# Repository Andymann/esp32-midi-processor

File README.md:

# esp32-midi-processor

esp32-based multitool. Routing, merging, realtime-manipulation of MIDI-data.  
This repo contains code, kicad-files and a BOM for (nearly) one-click order at [pcbway](https://https://pcbway-com).  

Find more details on the project, instructions on how to order your own pcbs and more at https://andyland.info/wordpress/esp32-midi-processor/

If you directly want to order your set of PCBs for this project feel free to

<p style="text-align:center; </p>

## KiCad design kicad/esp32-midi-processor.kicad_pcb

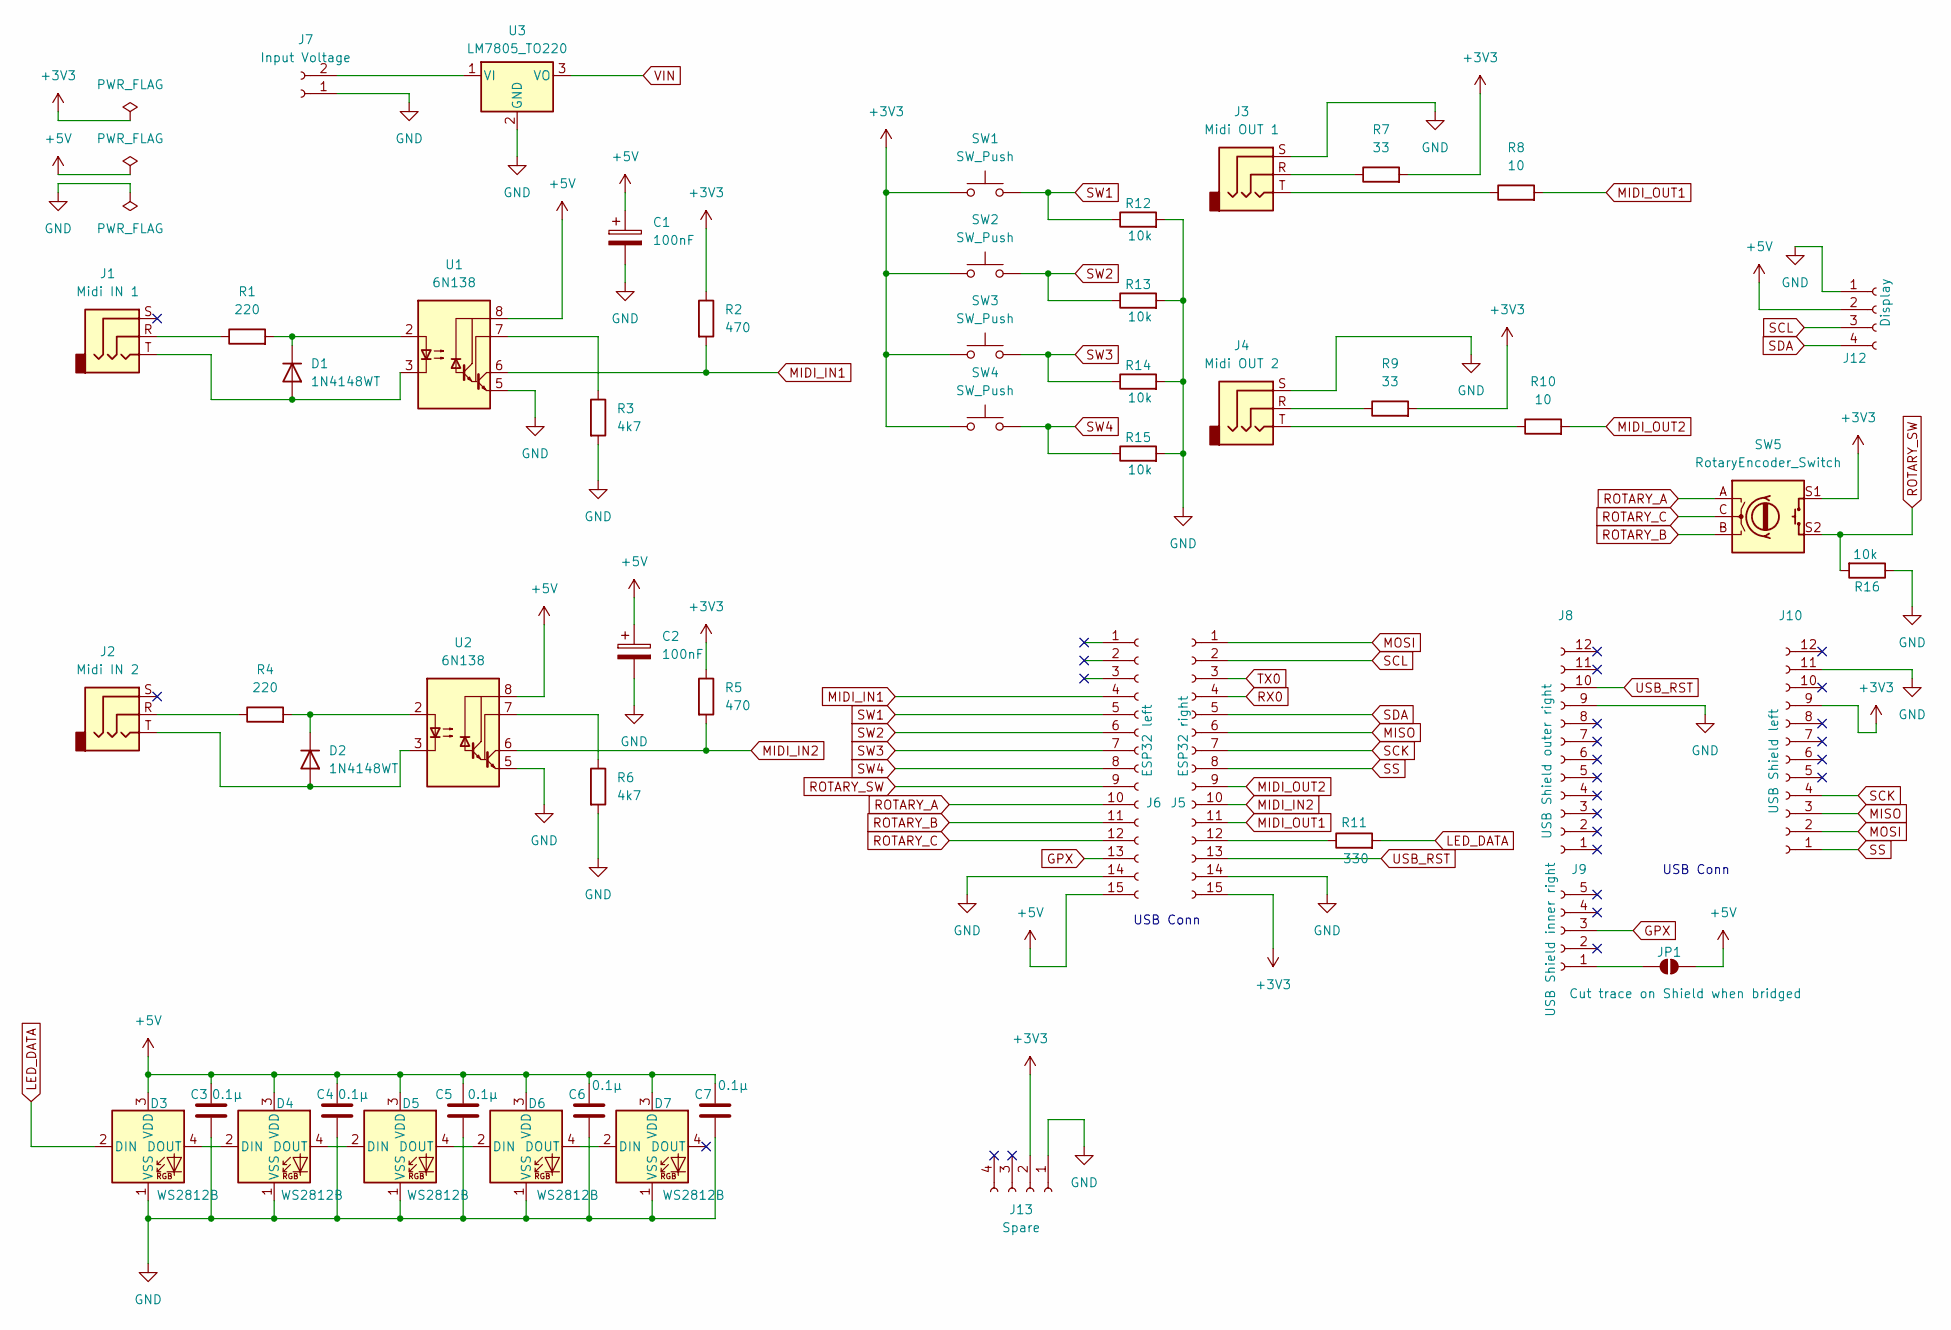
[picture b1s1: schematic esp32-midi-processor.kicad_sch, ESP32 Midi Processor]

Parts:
C1, C2: 100nF; C_0603_1608Metric
C3, C4, C5, C6, C7: 0.1µ; C_0603_1608Metric
D1, D2: 1N4148WT; D_SOD-523
D3, D4, D5, D6, D7: WS2812B; LED_WS2812B_PLCC4_5.0x5.0mm_P3.2mm
J1: Midi IN 1; Jack_3.5mm_CUI_SJ-3523-SMT_Horizontal
J2: Midi IN 2; Jack_3.5mm_CUI_SJ-3523-SMT_Horizontal
J3: Midi OUT 1; Jack_3.5mm_CUI_SJ-3523-SMT_Horizontal
J4: Midi OUT 2; Jack_3.5mm_CUI_SJ-3523-SMT_Horizontal
J5: ESP32 right; PinHeader_1x15_P2.54mm_Vertical
J6: ESP32 left; PinHeader_1x15_P2.54mm_Vertical
J7: Input Voltage; TerminalBlock_RND_205-00001_1x02_P5.00mm_Horizontal
J8: USB Shield outer right; PinHeader_1x12_P2.54mm_Vertical
J9: USB Shield inner right; PinHeader_1x05_P2.54mm_Vertical
J10: USB Shield left; PinHeader_1x12_P2.54mm_Vertical
J12: Display; PinHeader_1x04_P2.54mm_Vertical
J13: Spare; PinHeader_1x04_P2.54mm_Vertical
JP1: Cut trace on Shield when bridged; SolderJumper-2_P1.3mm_Open_RoundedPad1.0x1.5mm
R1, R4: 220; R_0603_1608Metric
R2, R5: 470; R_0603_1608Metric
R3, R6: 4k7; R_0603_1608Metric
R7, R9: 33; R_0603_1608Metric
R8, R10: 10; R_0603_1608Metric
R11: 330; R_0603_1608Metric
R12, R13, R14, R15, R16: 10k; R_0603_1608Metric
SW1, SW2, SW3, SW4: SW_Push; SW_PUSH-12mm_Wuerth-430476085716
SW5: RotaryEncoder_Switch; RotaryEncoder_Alps_EC11E-Switch_Vertical_H20mm
U1, U2: 6N138; SOP-8_6.605x9.655mm_P2.54mm
U3: LM7805_TO220; TO-220-3_Vertical

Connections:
+3V3: J5.15, J10.9, J13.2, R2.1, R5.1, R7.2, R9.2, SW1.1, SW2.1, SW3.1, SW4.1, SW5.S1
+5V: C1.1, C2.1, C3.1, C4.1, C5.1, C6.1, C7.1, D3.3 (VDD), D4.3 (VDD), D5.3 (VDD), D6.3 (VDD), D7.3 (VDD), J6.15, J12.2, JP1.2 (B), U1.8 (VCC), U2.8 (VCC)
GND: C1.2, C2.2, C3.2, C4.2, C5.2, C6.2, C7.2, D3.1 (VSS), D4.1 (VSS), D5.1 (VSS), D6.1 (VSS), D7.1 (VSS), J3.S, J4.S, J5.14, J6.14, J7.1, J8.9, J10.11, J12.1, J13.1, R3.2, R6.2, R12.2, R13.2, R14.2, R15.2, R16.1, U1.5 (GND), U2.5 (GND), U3.2 (GND)
GPX: J6.13, J9.3
LED_DATA: D3.2 (DIN), R11.2
MIDI_IN1: J6.4, R2.2, U1.6 (VO2)
MIDI_IN2: J5.10, R5.2, U2.6 (VO2)
MIDI_OUT1: J5.11, R8.2
MIDI_OUT2: J5.9, R10.2
MISO: J5.6, J10.3
MOSI: J5.1, J10.2
unnamed: D1.2 (A), J1.T, U1.3 (C2)
unnamed: D1.1 (K), R1.2, U1.2 (C1)
unnamed: D2.2 (A), J2.T, U2.3 (C2)
unnamed: D2.1 (K), R4.2, U2.2 (C1)
unnamed: D3.4 (DOUT), D4.2 (DIN)
unnamed: D4.4 (DOUT), D5.2 (DIN)
unnamed: D5.4 (DOUT), D6.2 (DIN)
unnamed: D6.4 (DOUT), D7.2 (DIN)
unnamed: J1.R, R1.1
unnamed: J2.R, R4.1
unnamed: J3.R, R7.1
unnamed: J3.T, R8.1
unnamed: J4.R, R9.1
unnamed: J4.T, R10.1
unnamed: J5.12, R11.1
unnamed: J7.2, U3.1 (VI)
unnamed: J9.1, JP1.1 (A)
unnamed: R3.1, U1.7 (VO1)
unnamed: R6.1, U2.7 (VO1)
ROTARY_A: J6.10, SW5.A
ROTARY_B: J6.11, SW5.B
ROTARY_C: J6.12, SW5.C
ROTARY_SW: J6.9, R16.2, SW5.S2
RX0: J5.4
SCK: J5.7, J10.4
SCL: J5.2, J12.3
SDA: J5.5, J12.4
SS: J5.8, J10.1
SW1: J6.5, R12.1, SW1.2
SW2: J6.6, R13.1, SW2.2
SW3: J6.7, R14.1, SW3.2
SW4: J6.8, R15.1, SW4.2
TX0: J5.3
USB_RST: J5.13, J8.10
VIN: U3.3 (VO)

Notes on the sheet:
USB Conn

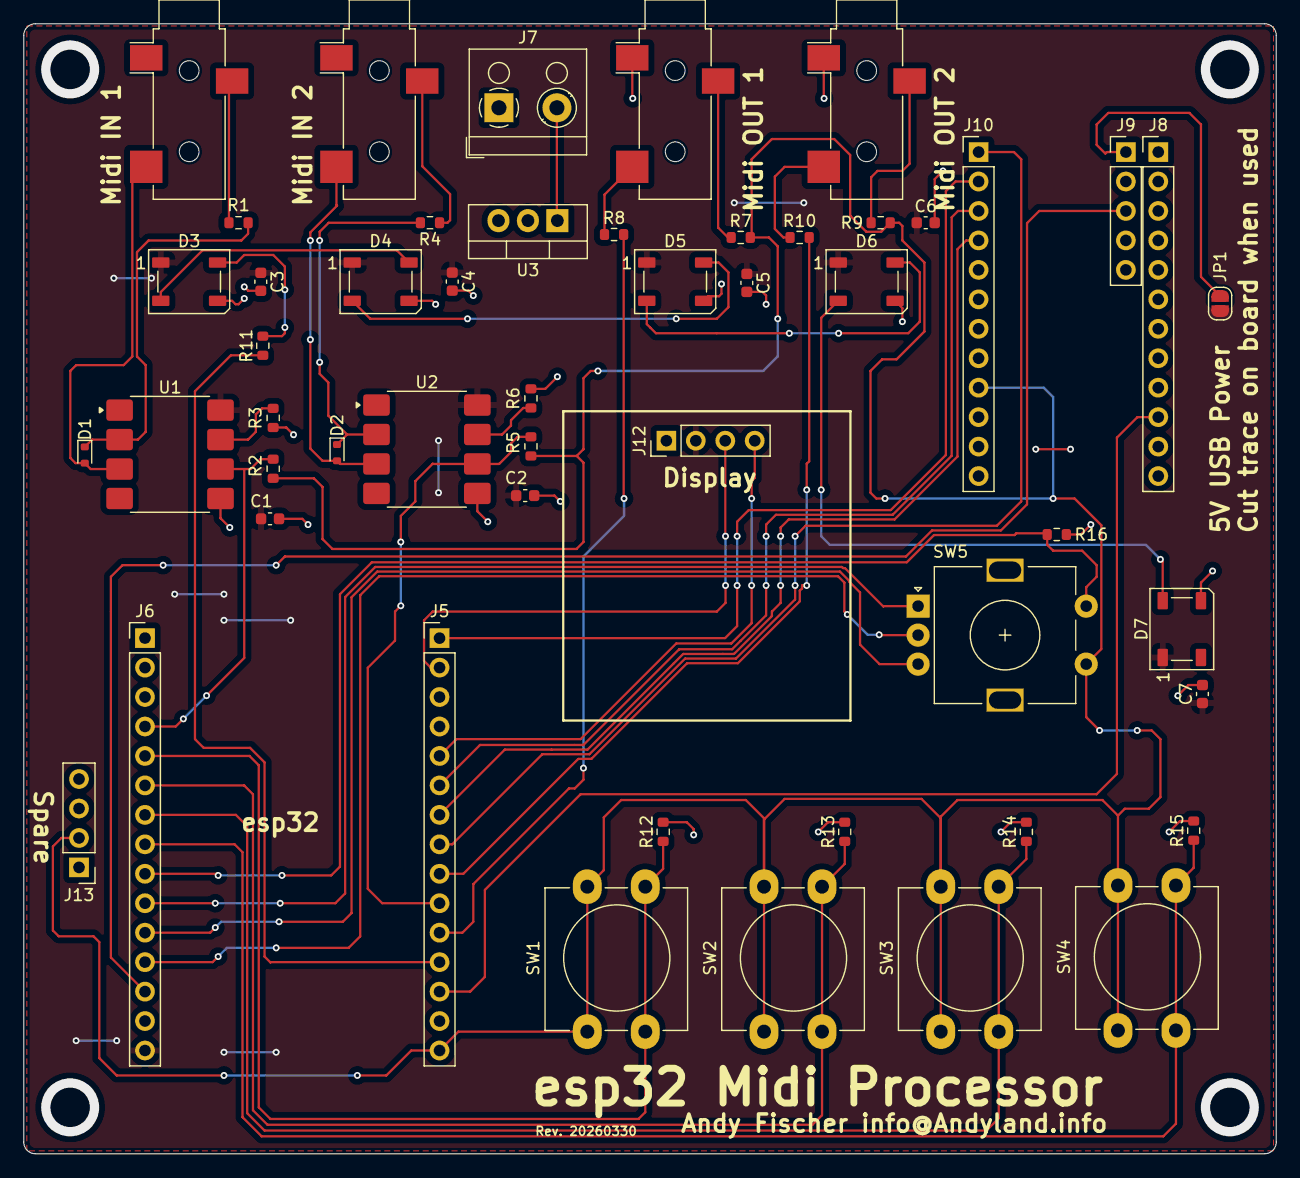
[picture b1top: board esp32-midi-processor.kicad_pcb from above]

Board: 2 copper layers, 108.0 x 97.4 mm, 51 parts (0 on the bottom side), 43 nets.

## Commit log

2025-09-16 add more stuff to schematic
2025-09-17 add switches, disconnect rotary encoder
2025-09-17 fix rotary encoder
2025-09-18 add footprints
2025-09-18 first pcb version
2025-09-18 new pcb revision
2025-09-22 Next PCB version
2025-09-22 finetune PCB layout
2025-09-24 fix usb shield's orientation
2025-11-03 fix orientation of pinheaders
2025-11-13 add 7805
2025-12-27 add title to schematic
2026-01-04 finish pcb
2026-02-22 rewrite logic with AI
2026-02-22 add features for output 2 and 3
2026-02-22 add per-output settings
2026-02-22 fix bug in appfeatures.h
2026-02-22 make selection eclusive per output
2026-02-22 implement scale mode for c maj
2026-02-22 restructure menu
2026-02-22 implement natural major and minor, pentatonic major and minor
2026-02-22 add preset functionality
2026-02-22 fintune preset handling
2026-02-22 make preset A load on startup
2026-02-22 fix bug when scale was set and velocity!=passthru
2026-02-22 bugfix: send note off on incoming note off
2026-02-22 add usb send, fix 0-velocity-handling
2026-02-23 make preset-load-screen look nice
2026-02-23 use struct for incoming midi packets
2026-02-23 create queue for up to 10 incoming midi events
2026-02-23 hand-over everything but note and ccs without processing
2026-02-23 pass-thru one-byte messages
2026-02-23 add clockfilter
2026-02-23 fix featurecount
2026-02-23 make preset-display nice
2026-02-25 manually retry usb init when buttons a and d are pressed for 3 seconds
2026-02-25 fix bug
2026-02-25 display message on manual usb.init()
2026-03-05 add 3mf file
2026-03-05 add info to readme.md
2026-03-30 add kicad files
2026-03-30 add image
2026-03-30 add info
2026-03-30 finetune README
2026-04-04 add diagrams
2026-04-05 add reviewed BOM
2026-04-05 add production files for easy order
2026-04-05 add link to pcbway in readme
